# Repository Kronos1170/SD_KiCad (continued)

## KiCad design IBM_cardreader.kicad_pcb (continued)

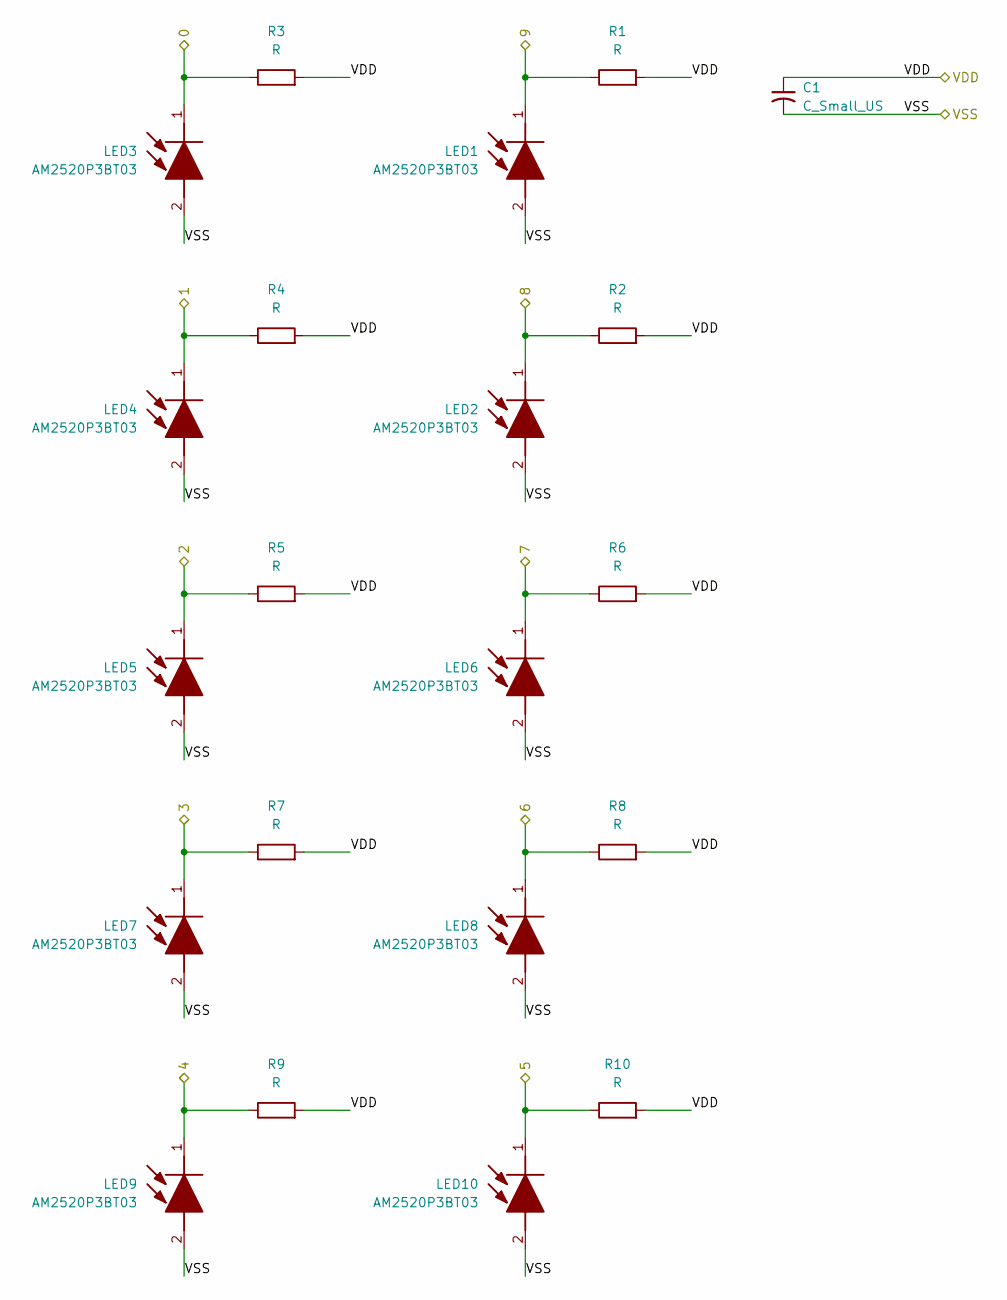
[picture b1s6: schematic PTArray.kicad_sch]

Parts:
C1: C_Small_US; C_Disc_D3.0mm_W1.6mm_P2.50mm
LED1, LED2, LED3, LED4, LED5, LED6, LED7, LED8, LED9, LED10: AM2520P3BT03; Kingbright; Mouser Part Number 604-AM2520P3BT03
R1, R2, R3, R4, R5, R6, R7, R8, R9, R10: R; R_Axial_DIN0207_L6.3mm_D2.5mm_P2.54mm_Vertical

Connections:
/SensorSelect/a2: LED5.1 (K), R5.1; also elsewhere on the board
/SensorSelect/a3: LED7.1 (K), R7.1; also elsewhere on the board
/SensorSelect/a4: LED9.1 (K), R9.1; also elsewhere on the board
/SensorSelect/a5: LED10.1 (K), R10.1; also elsewhere on the board
/SensorSelect/a6: LED8.1 (K), R8.1; also elsewhere on the board
/SensorSelect/a7: LED6.1 (K), R6.1; also elsewhere on the board
/SensorSelect/a8: LED2.1 (K), R2.1; also elsewhere on the board
/SensorSelect/a9: LED1.1 (K), R1.1; also elsewhere on the board
/SensorSelect/a_0: LED3.1 (K), R3.1; also elsewhere on the board
/SensorSelect/a_1: LED4.1 (K), R4.1; also elsewhere on the board
/VDD0: C1.1, R1.2, R2.2, R3.2, R4.2, R5.2, R6.2, R7.2, R8.2, R9.2, R10.2; also elsewhere on the board
/VSS0: C1.2, LED1.2 (A), LED2.2 (A), LED3.2 (A), LED4.2 (A), LED5.2 (A), LED6.2 (A), LED7.2 (A), LED8.2 (A), LED9.2 (A), LED10.2 (A); also elsewhere on the board

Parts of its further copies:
C2, C3, C4, C5: C_Small_US; C_Disc_D3.0mm_W1.6mm_P2.50mm
LED11, LED12, LED13, LED14, LED15, LED16, LED17, LED18, LED19, LED20, LED21, LED22, LED23, LED24, LED25, LED26, LED27, LED28, LED29, LED30, LED31, LED32, LED33, LED34, LED35, LED36, LED37, LED38, LED39, LED40, LED41, LED42, LED43, LED44, LED45, LED46, LED47, LED48, LED49, LED50: AM2520P3BT03; Kingbright; Mouser Part Number 604-AM2520P3BT03
R11, R12, R13, R14, R15, R16, R17, R18, R19, R20, R21, R22, R23, R24, R25, R26, R27, R28, R29, R30, R31, R32, R33, R34, R35, R36, R37, R38, R39, R40, R41, R42, R43, R44, R45, R46, R47, R48, R49, R50: R; R_Axial_DIN0207_L6.3mm_D2.5mm_P2.54mm_Vertical

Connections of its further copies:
/SensorSelect/b0: LED11.1 (K), R11.1; also elsewhere on the board
/SensorSelect/b1: LED12.1 (K), R12.1; also elsewhere on the board
/SensorSelect/b2: LED13.1 (K), R13.1; also elsewhere on the board
/SensorSelect/b3: LED14.1 (K), R14.1; also elsewhere on the board
/SensorSelect/b4: LED15.1 (K), R15.1; also elsewhere on the board
/SensorSelect/b5: LED20.1 (K), R20.1; also elsewhere on the board
/SensorSelect/b6: LED19.1 (K), R19.1; also elsewhere on the board
/SensorSelect/b7: LED18.1 (K), R18.1; also elsewhere on the board
/SensorSelect/b8: LED17.1 (K), R17.1; also elsewhere on the board
/SensorSelect/b9: LED16.1 (K), R16.1; also elsewhere on the board
/SensorSelect/c0: LED21.1 (K), R21.1; also elsewhere on the board
/SensorSelect/c1: LED22.1 (K), R22.1; also elsewhere on the board
/SensorSelect/c2: LED23.1 (K), R23.1; also elsewhere on the board
/SensorSelect/c3: LED24.1 (K), R24.1; also elsewhere on the board
/SensorSelect/c4: LED25.1 (K), R25.1; also elsewhere on the board
/SensorSelect/c5: LED30.1 (K), R30.1; also elsewhere on the board
/SensorSelect/c6: LED29.1 (K), R29.1; also elsewhere on the board
/SensorSelect/c7: LED28.1 (K), R28.1; also elsewhere on the board
/SensorSelect/c8: LED27.1 (K), R27.1; also elsewhere on the board
/SensorSelect/c9: LED26.1 (K), R26.1; also elsewhere on the board
/SensorSelect/d0: LED31.1 (K), R31.1; also elsewhere on the board
/SensorSelect/d1: LED32.1 (K), R32.1; also elsewhere on the board
/SensorSelect/d2: LED33.1 (K), R33.1; also elsewhere on the board
/SensorSelect/d3: LED34.1 (K), R34.1; also elsewhere on the board
/SensorSelect/d4: LED35.1 (K), R35.1; also elsewhere on the board
/SensorSelect/d5: LED40.1 (K), R40.1; also elsewhere on the board
/SensorSelect/d6: LED39.1 (K), R39.1; also elsewhere on the board
/SensorSelect/d7: LED38.1 (K), R38.1; also elsewhere on the board
/SensorSelect/d8: LED37.1 (K), R37.1; also elsewhere on the board
/SensorSelect/d9: LED36.1 (K), R36.1; also elsewhere on the board
/SensorSelect/e0: LED41.1 (K), R41.1; also elsewhere on the board
/SensorSelect/e1: LED42.1 (K), R42.1; also elsewhere on the board
/SensorSelect/e2: LED43.1 (K), R43.1; also elsewhere on the board
/SensorSelect/e3: LED44.1 (K), R44.1; also elsewhere on the board
/SensorSelect/e4: LED45.1 (K), R45.1; also elsewhere on the board
/SensorSelect/e5: LED50.1 (K), R50.1; also elsewhere on the board
/SensorSelect/e6: LED49.1 (K), R49.1; also elsewhere on the board
/SensorSelect/e7: LED48.1 (K), R48.1; also elsewhere on the board
/SensorSelect/e8: LED47.1 (K), R47.1; also elsewhere on the board
/SensorSelect/e9: LED46.1 (K), R46.1; also elsewhere on the board
/VDD0: C2.1, C3.1, C4.1, C5.1, R11.2, R12.2, R13.2, R14.2, R15.2, R16.2, R17.2, R18.2, R19.2, R20.2, R21.2, R22.2, R23.2, R24.2, R25.2, R26.2, R27.2, R28.2, R29.2, R30.2, R31.2, R32.2, R33.2, R34.2, R35.2, R36.2, R37.2, R38.2, R39.2, R40.2, R41.2, R42.2, R43.2, R44.2, R45.2, R46.2, R47.2, R48.2, R49.2, R50.2; also elsewhere on the board
/VSS0: C2.2, C3.2, C4.2, C5.2, LED11.2 (A), LED12.2 (A), LED13.2 (A), LED14.2 (A), LED15.2 (A), LED16.2 (A), LED17.2 (A), LED18.2 (A), LED19.2 (A), LED20.2 (A), LED21.2 (A), LED22.2 (A), LED23.2 (A), LED24.2 (A), LED25.2 (A), LED26.2 (A), LED27.2 (A), LED28.2 (A), LED29.2 (A), LED30.2 (A), LED31.2 (A), LED32.2 (A), LED33.2 (A), LED34.2 (A), LED35.2 (A), LED36.2 (A), LED37.2 (A), LED38.2 (A), LED39.2 (A), LED40.2 (A), LED41.2 (A), LED42.2 (A), LED43.2 (A), LED44.2 (A), LED45.2 (A), LED46.2 (A), LED47.2 (A), LED48.2 (A), LED49.2 (A), LED50.2 (A); also elsewhere on the board

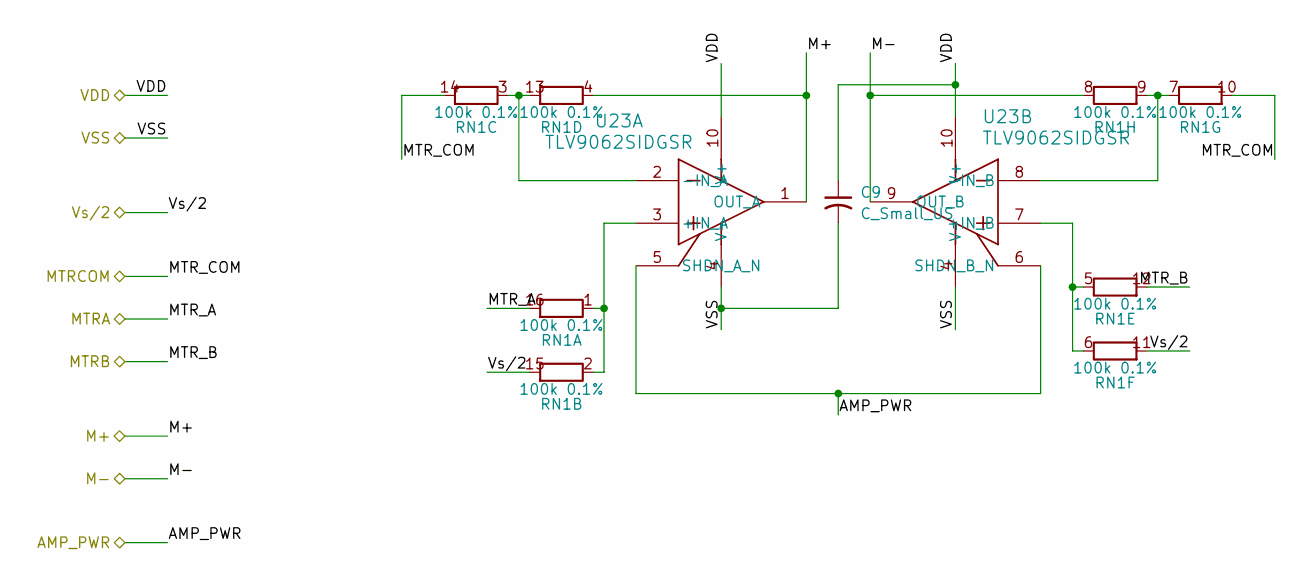
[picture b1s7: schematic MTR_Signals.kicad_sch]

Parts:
C9: C_Small_US; C_Disc_D3.0mm_W1.6mm_P2.50mm
RN1: 100k 0.1%; DIP-16_W7.62mm
U23: TLV9062SIDGSR; TLV9062S_carrier

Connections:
/AMP_PWR: U23.5 (SHDN_A_N), U23.6 (SHDN_B_N); also elsewhere on the board
/Motor/MTR_+: RN1.16; also elsewhere on the board
/Motor/MTR_-: RN1.12; also elsewhere on the board
/Motor/MTR_COM: RN1.10, RN1.14; also elsewhere on the board
/VDD: C9.1, U23.10 (V+); also elsewhere on the board
/VSS: C9.2, RN1.4, RN1.8, U23.1 (OUT_A), U23.4 (V-), U23.9 (OUT_B); also elsewhere on the board
/Vs/2: RN1.11, RN1.15; also elsewhere on the board
unnamed: RN1.1, RN1.2, U23.3 (+IN_A)
unnamed: RN1.3, RN1.13, U23.2 (-IN_A)
unnamed: RN1.5, RN1.6, U23.7 (+IN_B)
unnamed: RN1.7, RN1.9, U23.8 (-IN_B)

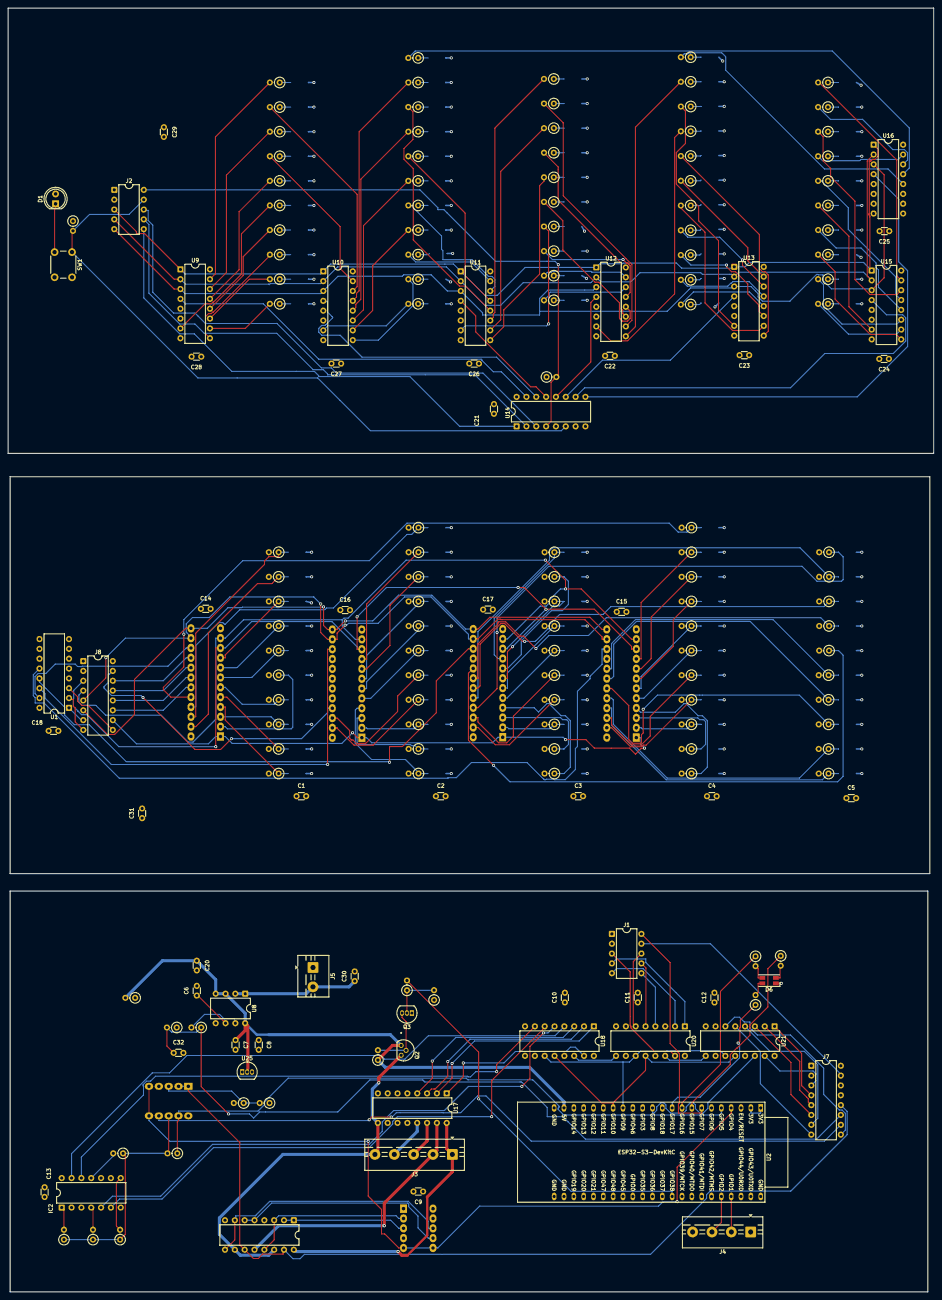
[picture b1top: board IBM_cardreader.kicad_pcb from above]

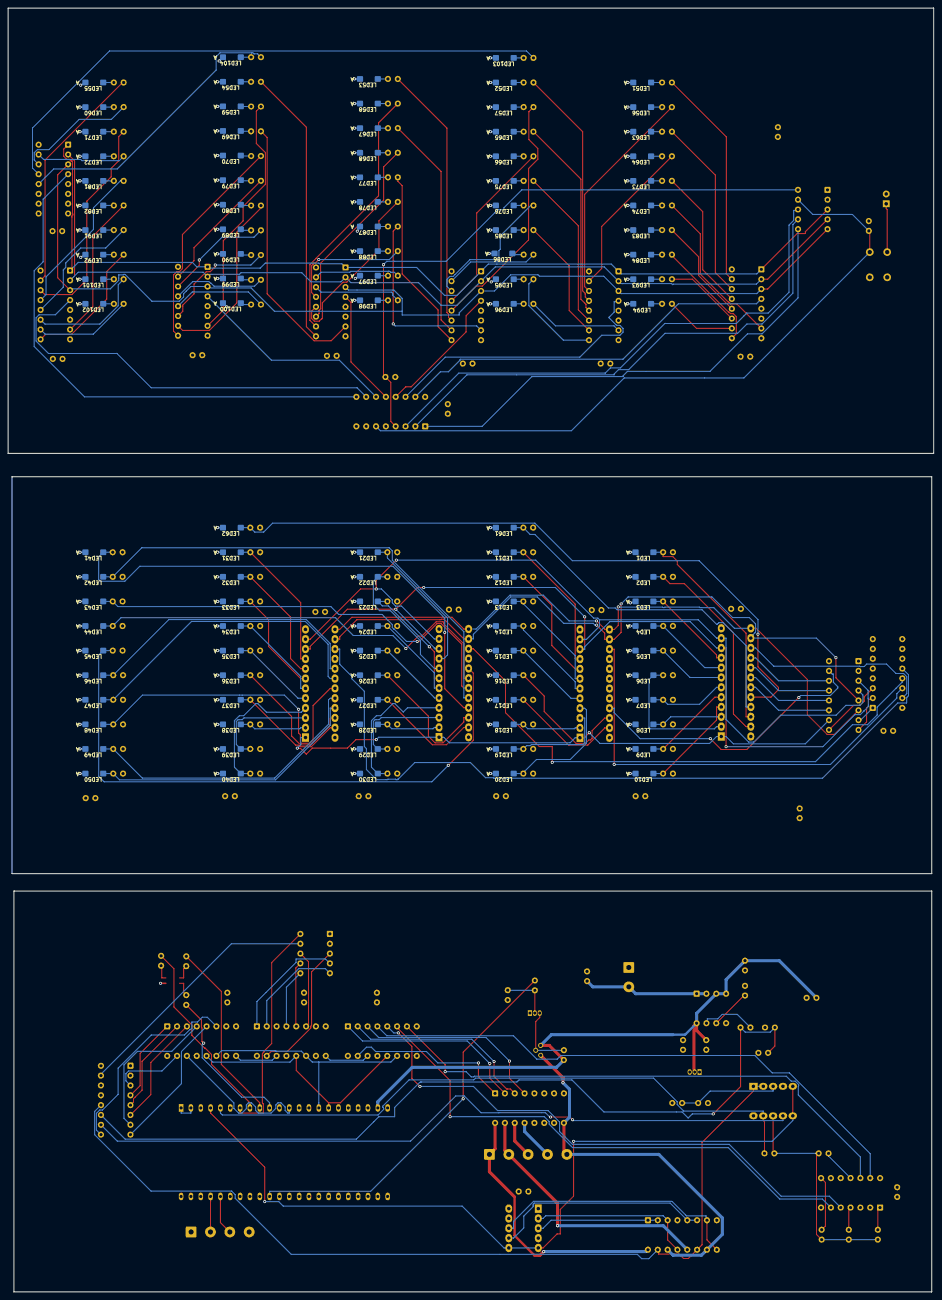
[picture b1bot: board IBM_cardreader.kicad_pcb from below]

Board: 4 copper layers, 239.0 x 331.5 mm, 293 parts (104 on the bottom side), 259 nets.

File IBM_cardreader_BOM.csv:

"Reference","Value","Datasheet","Footprint","Qty","DNP"
"C1,C2,C3,C4,C5,C6,C7,C8,C9,C10,C11,C12,C13,C14,C15,C16,C17,C18,C19,C20,C21,C22,C23,C24,C25,C26,C27,C28,C29,C31","C_Small_US","","Capacitor_SMD:CP_Elec_3x5.3","30",""
"D1","LED","","LED_THT:LED_D5.0mm","1",""
"D6","LED_ARGB","","LED_SMD:LED_RGB_1210","1",""
"IC1,IC2","CD4066BE","https://datasheet.datasheetarchive.com/originals/distributor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","Package_DIP:DIP-16_W7.62mm","2",""
"J1,J2","Conn_01x10_Pin","","TerminalBlock:TerminalBlock_MaiXu_MX126-5.0-10P_1x10_P5.00mm","2",""
"J3","Conn_01x05_Pin","","TerminalBlock:TerminalBlock_MaiXu_MX126-5.0-05P_1x05_P5.00mm","1",""
"J4","Conn_01x04_Pin","","TerminalBlock:TerminalBlock_MaiXu_MX126-5.0-04P_1x04_P5.00mm","1",""
"J5","Conn_01x02_Pin","","TerminalBlock:TerminalBlock_MaiXu_MX126-5.0-02P_1x02_P5.00mm","1",""
"J7,J8","Conn_01x15_Pin","","TerminalBlock:TerminalBlock_MaiXu_MX126-5.0-15P_1x15_P5.00mm","2",""
"LED1,LED2,LED3,LED4,LED5,LED6,LED7,LED8,LED9,LED10,LED11,LED12,LED13,LED14,LED15,LED16,LED17,LED18,LED19,LED20,LED21,LED22,LED23,LED24,LED25,LED26,LED27,LED28,LED29,LED30,LED31,LED32,LED33,LED34,LED35,LED36,LED37,LED38,LED39,LED40,LED41,LED42,LED43,LED44,LED45,LED46,LED47,LED48,LED49,LED50,LED61,LED62","AM2520P3BT03","","IBM_cardreader:Kingbright","52",""
"LED51,LED52,LED53,LED54,LED55,LED56,LED57,LED58,LED59,LED60,LED63,LED64,LED65,LED66,LED67,LED68,LED69,LED70,LED71,LED72,LED73,LED74,LED75,LED76,LED77,LED78,LED79,LED80,LED81,LED82,LED83,LED84,LED85,LED86,LED87,LED88,LED89,LED90,LED91,LED92,LED93,LED94,LED95,LED96,LED97,LED98,LED99,LED100,LED101,LED102,LED103,LED104","AM2520F3C03-P22","http://www.kingbrightusa.com/images/catalog/SPEC/AM2520F3C03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","IBM_cardreader:Kingbright","52",""
"Q2,Q4,Q6","FQP27P06","https://www.onsemi.com/pub/Collateral/FQP27P06-D.PDF","Package_TO_SOT_THT:TO-220-3_Vertical","3",""
"Q3,Q5","2N3904","https://www.onsemi.com/pub/Collateral/2N3903-D.PDF","Package_TO_SOT_THT:TO-92_Inline","2",""
"R1,R2,R3,R4,R5,R6,R7,R8,R9,R10,R11,R12,R13,R14,R15,R16,R17,R18,R19,R20,R21,R22,R23,R24,R25,R26,R27,R28,R29,R30,R31,R32,R33,R34,R35,R36,R37,R38,R39,R40,R41,R42,R43,R44,R45,R46,R47,R48,R49,R50,R51,R52,R53,R54,R55,R56,R57,R58,R59,R60,R61,R62,R63,R64,R65,R66,R67,R68,R69,R70,R71,R72,R73,R74,R75,R76,R77,R78,R79,R80,R81,R82,R83,R84,R85,R86,R87,R88,R89,R90,R91,R92,R93,R94,R95,R96,R97,R98,R99,R100,R101,R102,R103,R104,R105,R106,R107,R108,R109,R110,R111,R112,R113,R114,R115,R116,R117,R120,R121,R122,R123,R124,R125,R126,R127,R130,R131,R139,R140,R141,R146,R147,R148,R150","R","","Resistor_SMD:R_0508_1220Metric,Resistor_SMD:R_1020_2550Metric","134",""
"RV1,RV2,RV3,RV4,RV5,RV6,RV7,RV8,RV9,RV10,RV11,RV12,RV13,RV14,RV15,RV16,RV17,RV18,RV19,RV20,RV21,RV22,RV23,RV24,RV25,RV26,RV27,RV28,RV29,RV30,RV31,RV32,RV33,RV34,RV35,RV36,RV37,RV38,RV39,RV40,RV41,RV42,RV43,RV44,RV45,RV46,RV47,RV48,RV49,RV50,RV51,RV52","R_Potentiometer","","Potentiometer_SMD:Potentiometer_Bourns_3314J_Vertical","52",""
"SW1","SW_Push_Dual","","Button_Switch_THT:SW_PUSH_6mm","1",""
"U1,U9,U10,U11,U12,U13,U14,U15,U16","74HC138","http://www.ti.com/lit/ds/symlink/cd74hc238.pdf","Package_DIP:DIP-16_W7.62mm","9",""
"U2","ESP32-S3-DevKitC","","Espressif:ESP32-S3-DevKitC","1",""
"U4,U5,U6,U7","CD74HC4067M","http://www.ti.com/lit/ds/symlink/cd74hc4067.pdf","IBM_cardreader:CD74HC4067_carrier","4",""
"U8","ACS724xLCTR-05AB","http://www.allegromicro.com/~/media/Files/Datasheets/ACS724-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","IBM_cardreader:ACS724_Breakout_socket","1",""
"U17","ULN2003","http://www.ti.com/lit/ds/symlink/uln2003a.pdf","Package_DIP:DIP-16_W7.62mm","1",""
"U18,U20,U21","74HC595","http://www.ti.com/lit/ds/symlink/sn74hc595.pdf","Package_DIP:DIP-16_W7.62mm","3",""
"U22,U23","TLV9062SIDGSR","https://www.ti.com/lit/gpn/tlv9062","IBM_cardreader:TLV9062S_carrier","2",""
"U25","MCP1700x-330xxTO","http://ww1.microchip.com/downloads/en/DeviceDoc/20001826D.pdf","Package_TO_SOT_THT:TO-92_Inline","1",""
